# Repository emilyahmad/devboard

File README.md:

# Devboard

A simple devboard with some cute curious george motifs - my first hardware project/PCB, built using @KaiPereira's starter guide on stasis. Like any good devboard, the monkeyboard contains an SoC, memory, power management and I/O interfaces: it receives power via its USB-C connector port, maintains a quad SPI flash memory IC for data storage, 2 multipurpose switches, a crystal oscillator for precise electrical frequencies, and the star of the show, the RP2040 as its MCU.

### Assembled

| Front                              | Back                                 | Plugged in                               |
| ---------------------------------- | ------------------------------------ | ---------------------------------------- |
|  |  |  |

### Design

| Schematic                                                                                             | PCB                                                                                       | 3D Render                                                                                     |
| ----------------------------------------------------------------------------------------------------- | ----------------------------------------------------------------------------------------- | --------------------------------------------------------------------------------------------- |
|  |  |  |

### BOM

| Item                                 | Purpose                      | Quantity | Cost    | Source                               |
| ------------------------------------ | ---------------------------- | -------- | ------- | ------------------------------------ |
| C1, C2                               | 10uF decoupling capacitor    | 2        | $0.0800 | JLCPCB Basic (CL10A106KP8NNNC)       |
| C3, C18                              | 1uF decoupling capacitor     | 2        | $0.0660 | JLCPCB Extended (GRM155R60J105KE19D) |
| C4, C5, C19, C20, C22, C23, C24, C26 | 0.1uF decoupling capacitor   | 8        | $0.0845 | JLCPCB Basic (CL05B104KO5NNNC)       |
| C15, C16                             | 33pF crystal load capacitor  | 2        | $0.0130 | JLCPCB Basic (0402CG330J500NT)       |
| C17, C21, C25                        | 0.1uF decoupling capacitor   | 3        | $0.0845 | JLCPCB Basic (CL05B104KO5NNNC)       |
| J1                                   | USB-C receptacle             | 1        | $0.9155 | JLCPCB Extended (TYPE-C-31-M-12)     |
| J2, J3                               | 20-pin GPIO header           | 2        | —       | Solder yourself                      |
| J4                                   | 3-pin SWD debug header       | 1        | —       | Solder yourself                      |
| R1, R2                               | 5.1K CC pull-down resistor   | 2        | $0.0090 | JLCPCB Basic (0402WGF5101TCE)        |
| R3, R4                               | 27Ω USB termination resistor | 2        | $0.0176 | JLCPCB Extended (0402WGF270JTCE)     |
| R5, R7, R8                           | 1K resistor                  | 3        | $0.0150 | JLCPCB Extended (RCT021KFLF)         |
| R6                                   | 10K pull-up resistor         | 1        | $0.0065 | JLCPCB Basic (0402WGF1002TCE)        |
| SW1, SW2                             | Push button                  | 2        | $0.5550 | JLCPCB Basic (TS-1088-AR02016)       |
| U1                                   | MCP1700 3.3V LDO regulator   | 1        | $2.4285 | JLCPCB Extended (MCP1700T-3302E/TT)  |
| U2                                   | RP2040 microcontroller       | 1        | $4.8810 | JLCPCB Extended (RP2040)             |
| U3                                   | W25Q16 16Mbit flash memory   | 1        | $6.3910 | JLCPCB Extended (W25Q16JVZPIQ TR)    |
| Y1                                   | 12MHz crystal oscillator     | 1        | $0.8382 | JLCPCB Extended (XJHCELNANF-12MHZ)   |

Total: $16.38

<!--
reference
|RP2040|$0.94|https://www.lcsc.com/product-detail/C2040.html?s_z=s_p_RP2040&spm=wm.ssy.bg.0.xh&lcsc_vid=E1ENUAdXFlVdBAVSQFBZUQJQRFEMVgIFEgVcAgBRQgQxVlNRQFNbUVBfR1haUjsOAxUeFF5JWBYZEEoKFBINSQcJGk4%3D|
|Crystal oscillator|$0.07|https://www.lcsc.com/product-detail/C9002.html?s_z=s_q_CRYSTAL%252012MHZ&spm=wm.ssy.bg.0.xh&lcsc_vid=E1ENUAdXFlVdBAVSQFBZUQJQRFEMVgIFEgVcAgBRQgQxVlNRQFNbUVFTRlVXXzsOAxUeFF5JWBYZEEoKFBINSQcJGk4eFQsCAgIaSgADAwAHC0slRVFaV0oOAwwC|
|MCP1700 LDO, 3.3V|$0.98|https://www.lcsc.com/product-detail/C39051.html?s_z=n_q_mcp1700%2520tt&spm=wm.ssy.bg.16.xh&lcsc_vid=E1ENUAdXFlVdBAVSQFBZUQJQRFEMVgIFEgVcAgBRQgQxVlNRQFNbUVJRR1hcXjsOAxUeFF5JWBYZEEoKFBINSQcJGk4dAgUUFAk%3D|
|USB-C port, 16-pin|$0.08|https://www.lcsc.com/product-detail/C2988369.html?s_z=n_q_usb%2520c%252016&spm=wm.ssy.bg.0.xh&lcsc_vid=E1ENUAdXFlVdBAVSQFBZUQJQRFEMVgIFEgVcAgBRQgQxVlNRQFNbUVNSRVVYVzsOAxUeFF5JWBYZEEoKFBINSQcJGk4eFQsCAgIaSgADAwAHC0slRFheUlVIHxUDCw%3D%3D|
|W25Q128JVSIQ flash memory|$1.96|https://www.lcsc.com/product-detail/C97521.html?s_z=s_q_W25Q128JVSIQ&spm=wm.ssy.bg.0.xh&lcsc_vid=E1ENUAdXFlVdBAVSQFBZUQJQRFEMVgIFEgVcAgBRQgQxVlNRQFNbUVxWRFlWVTsOAxUeFF5JWBYZEEoKFBINSQcJGk4eFQsCAgIaSgADAwAHC0slRVhWX1dQTk8GEwkK|
|PCM5102A DAC|$1.02|https://www.lcsc.com/product-detail/C107671.html?s_z=n_q_pcm5102a&spm=wm.ssy.bg.1.xh&lcsc_vid=E1ENUAdXFlVdBAVSQFBZUQJQRFEMVgIFEgVcAgBRQgQxVlNRQFNbUV1XRVlaVjsOAxUeFF5JWBYZEEoKFBINSQcJGk4dAgUUFAk%3D|
|PAM8302AAD speaker amplifier|$0.21|https://www.lcsc.com/product-detail/C112137.html?s_z=n_q_pam8302aad&spm=wm.ssy.bg.0.xh&lcsc_vid=E1ENUAdXFlVdBAVSQFBZUQJQRFEMVgIFEgVcAgBRQgQxVlNRQFNbUV1SQFJbUzsOAxUeFF5JWBYZEEoKFBINSQcJGk4eFQsCAgIaSgADAwAHC0slRlFZUVNXWQkaCgg%3D|
|BQ25185 battery charging IC|$1.66|https://www.lcsc.com/product-detail/C19725033.html?s_z=s_p_BQ25185DLHR&spm=wm.ssy.bg.0.xh&lcsc_vid=E1ENUAdXFlVdBAVSQFBZUQJQRFEMVgIFEgVcAgBRQgQxVlNRQFNbUV1fQ1RWVzsOAxUeFF5JWBYZEEoKFBINSQcJGk4eFQsCAgIaSgADAwAHC0slRlBcVldRWQkaCgg%3D|
|SMD tactile switch, 6x6mm|$0.03|https://www.lcsc.com/product-detail/C49234152.html?s_z=n_q_5x5mm%2520button&spm=wm.ssy.bg.0.xh&lcsc_vid=RlQIVAdXEVQKUwJREwNdVlQAEQNaUAUCTlNbAgdURlMxVlNRQFJcUFFUTlhdUDsOAxUeFF5JWBYZEEoKFBINSQcJGk4%3D|
|Pin headers|$0.38|https://www.lcsc.com/product-detail/C2938459.html?s_z=h_q_pin%2520headers%252001x20&spm=wm.ssy.bg.1.xh&lcsc_vid=RlQIVAdXEVQKUwJREwNdVlQAEQNaUAUCTlNbAgdURlMxVlNRQFJcX1dVQFdZVTsOAxUeFF5JWBYZEEoKFBINSQcJGk4eFQsCAgIaSgADAwAHC0slRVhdX1BUQ08GEwkK|
|PCB|$0.42|https://cart.jlcpcb.com/quote?stencilLayer=2&stencilWidth=21&stencilLength=54&stencilCounts=5&plateType=1|
|Stencil|$3.05|https://cart.jlcpcb.com/quote?stencilLayer=2&stencilWidth=21&stencilLength=54&stencilCounts=5&plateType=1|

Total: $10.81 ($7.76 w/o stencil)

# Notes

meow
-

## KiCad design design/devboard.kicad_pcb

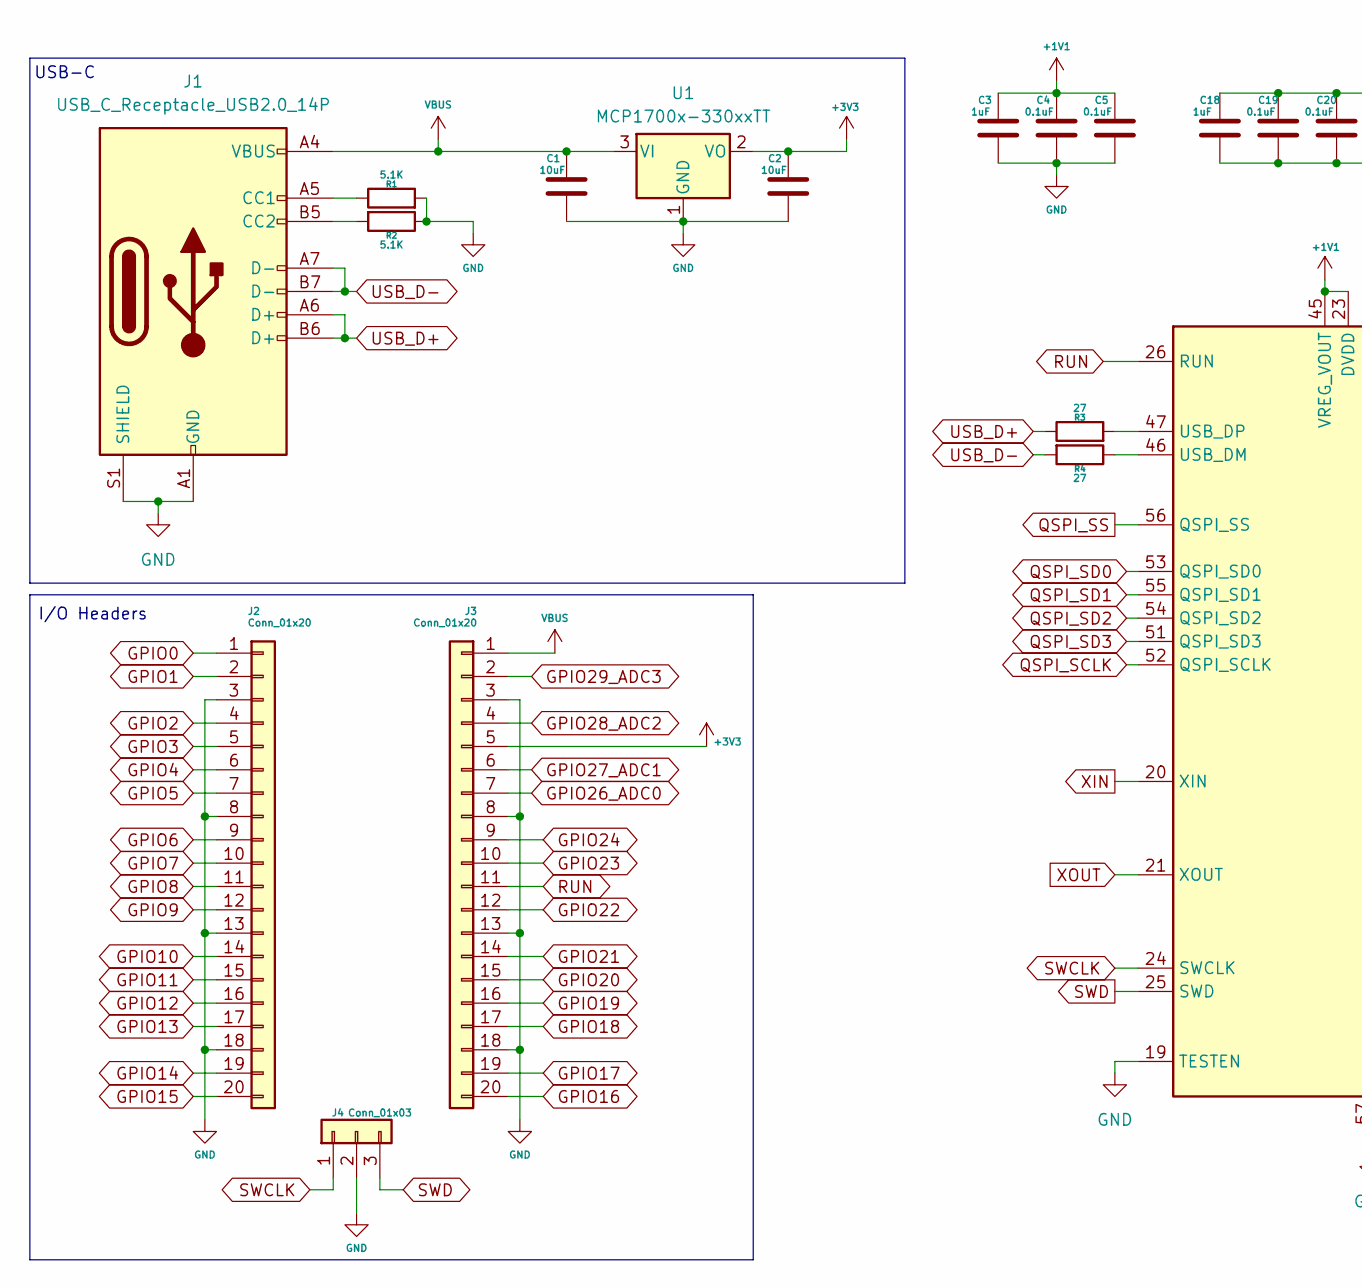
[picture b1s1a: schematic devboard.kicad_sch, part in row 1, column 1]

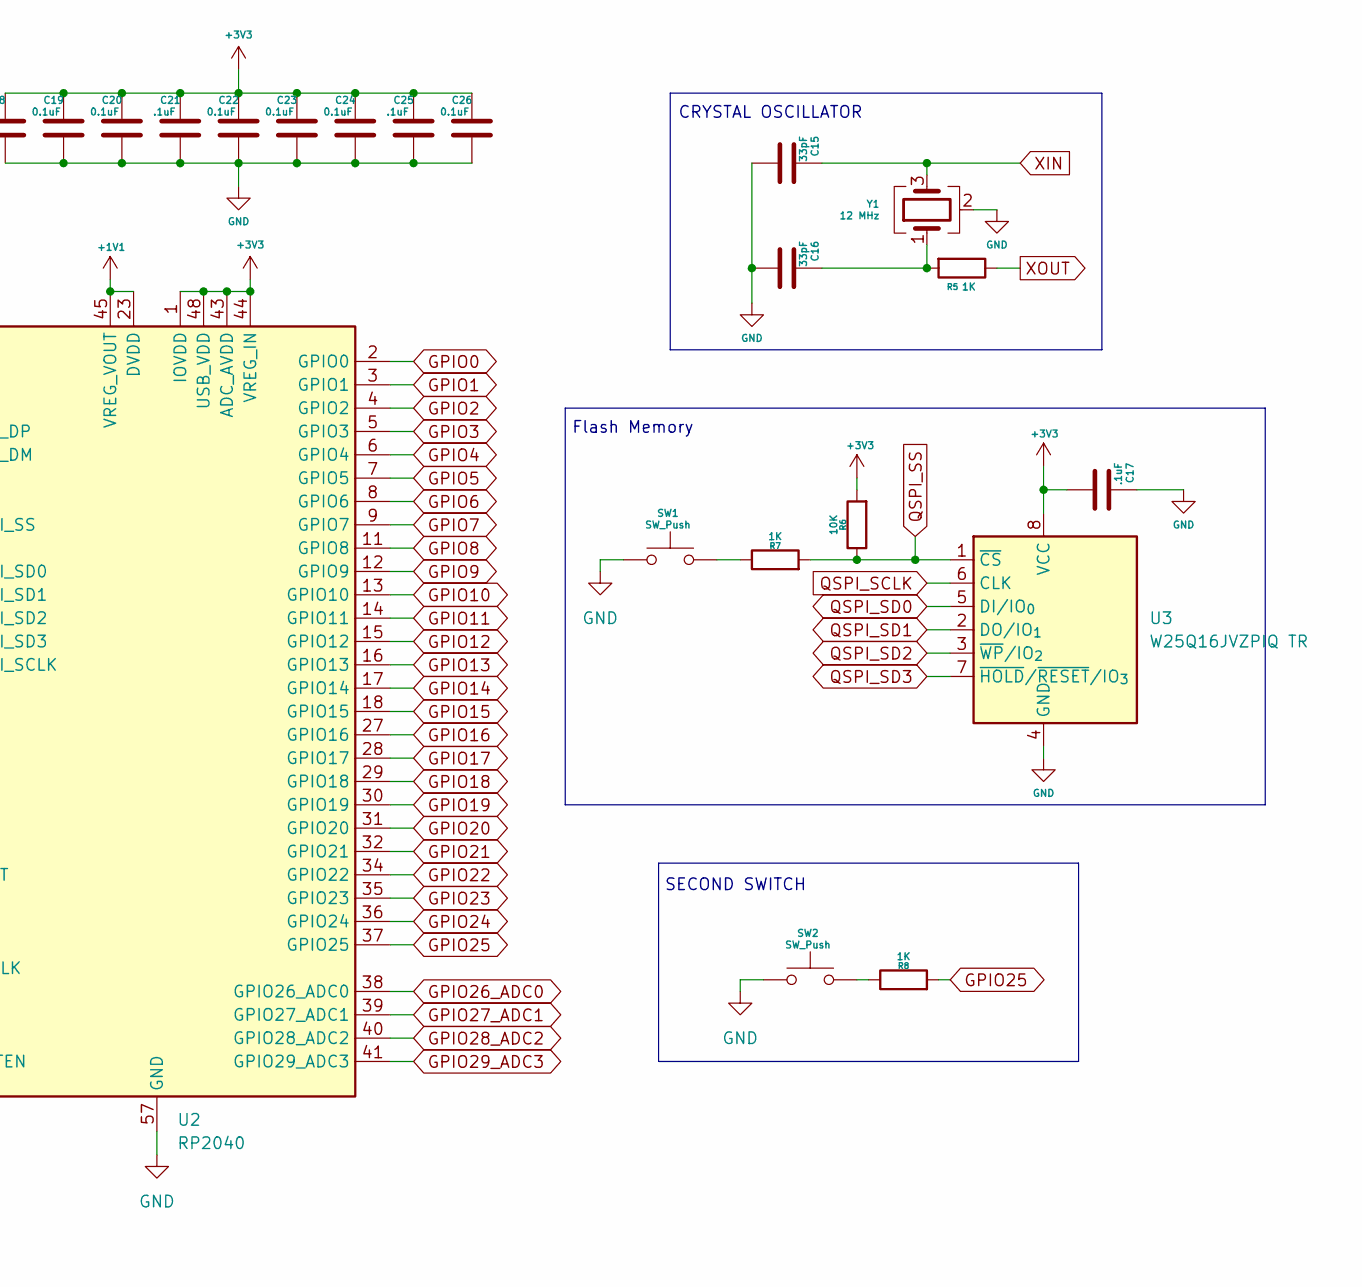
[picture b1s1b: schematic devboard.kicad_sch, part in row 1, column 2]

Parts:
C1, C2: 10uF; C_0201_0603Metric
C3, C18: 1uF; C_0402_1005Metric
C4, C5, C19, C20, C22, C23, C24, C26: 0.1uF; C_0402_1005Metric
C15, C16: 33pF; C_0402_1005Metric
C17, C21, C25: .1uF; C_0402_1005Metric
J1: USB_C_Receptacle_USB2.0_14P; USB_C_Receptacle_HRO_TYPE-C-31-M-12
J2, J3: Conn_01x20; PinHeader_1x20_P2.54mm_Vertical
J4: Conn_01x03; PinHeader_1x03_P2.54mm_Vertical
R1, R2: 5.1K; C_0402_1005Metric
R3, R4: 27; C_0402_1005Metric
R5, R7, R8: 1K; C_0402_1005Metric
R6: 10K; C_0402_1005Metric
SW1, SW2: SW_Push; SW_Push_SPST_NO_Alps_SKRK
U1: MCP1700x-330xxTT; SOT-23
U2: RP2040; QFN-56-1EP_7x7mm_P0.4mm_EP3.2x3.2mm
U3: W25Q16JVZPIQ TR; Winbond_USON-8-1EP_3x2mm_P0.5mm_EP0.2x1.6mm
Y1: 12 MHz; Crystal_SMD_3225-4Pin_3.2x2.5mm

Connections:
+1V1: C3.2, C4.2, C5.2, U2.23 (DVDD), U2.45 (VREG_VOUT), U2.50 (DVDD)
+3V3: C2.2, C17.1, C18.2, C19.2, C20.2, C21.2, C22.2, C23.2, C24.2, C25.2, C26.2, J3.5, R6.2, U1.2 (VO), U2.1 (IOVDD), U2.10 (IOVDD), U2.22 (IOVDD), U2.33 (IOVDD), U2.42 (IOVDD), U2.43 (ADC_AVDD), U2.44 (VREG_IN), U2.48 (USB_VDD), U2.49 (IOVDD), U3.8 (VCC)
GND: C1.1, C2.1, C3.1, C4.1, C5.1, C15.1, C16.1, C17.2, C18.1, C19.1, C20.1, C21.1, C22.1, C23.1, C24.1, C25.1, C26.1, J1.A1 (GND), J1.A12 (GND), J1.B1 (GND), J1.B12 (GND), J1.S1 (SHIELD), J2.3, J2.8, J2.13, J2.18, J3.3, J3.8, J3.13, J3.18, J4.2, R1.2, R2.1, SW1.1, SW2.1, U1.1 (GND), U2.19 (TESTEN), U2.57 (GND), U3.4 (GND), Y1.2 (G), Y1.4 (G)
GPIO0: J2.1, U2.2 (GPIO0)
GPIO1: J2.2, U2.3 (GPIO1)
GPIO2: J2.4, U2.4 (GPIO2)
GPIO3: J2.5, U2.5 (GPIO3)
GPIO4: J2.6, U2.6 (GPIO4)
GPIO5: J2.7, U2.7 (GPIO5)
GPIO6: J2.9, U2.8 (GPIO6)
GPIO7: J2.10, U2.9 (GPIO7)
GPIO8: J2.11, U2.11 (GPIO8)
GPIO9: J2.12, U2.12 (GPIO9)
GPIO10: J2.14, U2.13 (GPIO10)
GPIO11: J2.15, U2.14 (GPIO11)
GPIO12: J2.16, U2.15 (GPIO12)
GPIO13: J2.17, U2.16 (GPIO13)
GPIO14: J2.19, U2.17 (GPIO14)
GPIO15: J2.20, U2.18 (GPIO15)
GPIO16: J3.20, U2.27 (GPIO16)
GPIO17: J3.19, U2.28 (GPIO17)
GPIO18: J3.17, U2.29 (GPIO18)
GPIO19: J3.16, U2.30 (GPIO19)
GPIO20: J3.15, U2.31 (GPIO20)
GPIO21: J3.14, U2.32 (GPIO21)
GPIO22: J3.12, U2.34 (GPIO22)
GPIO23: J3.10, U2.35 (GPIO23)
GPIO24: J3.9, U2.36 (GPIO24)
GPIO25: R8.2, U2.37 (GPIO25)
GPIO26_ADC0: J3.7, U2.38 (GPIO26_ADC0)
GPIO27_ADC1: J3.6, U2.39 (GPIO27_ADC1)
GPIO28_ADC2: J3.4, U2.40 (GPIO28_ADC2)
GPIO29_ADC3: J3.2, U2.41 (GPIO29_ADC3)
unnamed: C16.2, R5.2, Y1.1
unnamed: J1.A5 (CC1), R1.1
unnamed: J1.B5 (CC2), R2.2
unnamed: R7.1, SW1.2
unnamed: R8.1, SW2.2
unnamed: R4.1, U2.46 (USB_DM)
unnamed: R3.2, U2.47 (USB_DP)
QSPI_SCLK: U2.52 (QSPI_SCLK), U3.6 (CLK)
QSPI_SD0: U2.53 (QSPI_SD0), U3.5 (DI/IO_{0})
QSPI_SD1: U2.55 (QSPI_SD1), U3.2 (DO/IO_{1})
QSPI_SD2: U2.54 (QSPI_SD2), U3.3 (~WP/IO_{2})
QSPI_SD3: U2.51 (QSPI_SD3), U3.7 (~HOLD/~RESET/IO_{3})
QSPI_SS: R6.1, R7.2, U2.56 (QSPI_SS), U3.1 (~CS)
RUN: J3.11, U2.26 (RUN)
SWCLK: J4.1, U2.24 (SWCLK)
SWD: J4.3, U2.25 (SWD)
USB_D+: J1.A6 (D+), J1.B6 (D+), R3.1
USB_D-: J1.A7 (D-), J1.B7 (D-), R4.2
VBUS: C1.2, J1.A4 (VBUS), J1.A9 (VBUS), J1.B4 (VBUS), J1.B9 (VBUS), J3.1, U1.3 (VI)
XIN: C15.2, U2.20 (XIN), Y1.3
XOUT: R5.1, U2.21 (XOUT)

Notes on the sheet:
USB-C
SECOND SWITCH
Flash Memory
CRYSTAL OSCILLATOR
I/O Headers

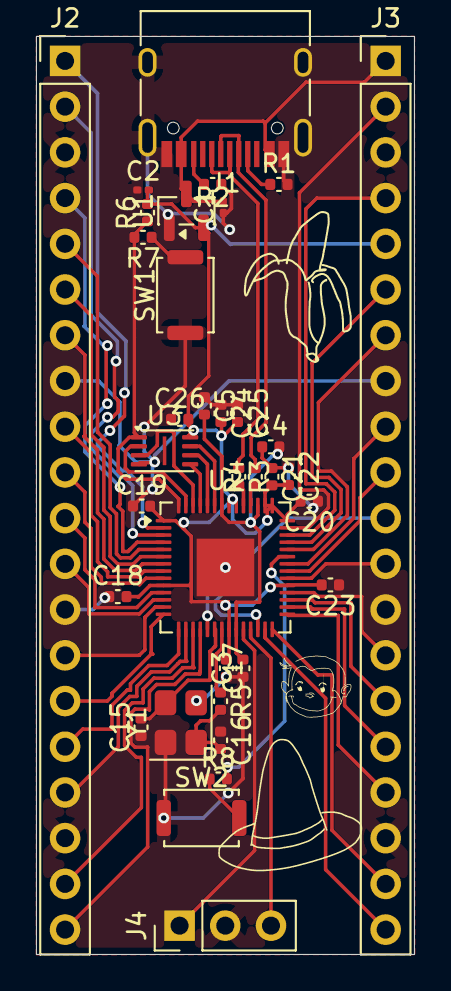
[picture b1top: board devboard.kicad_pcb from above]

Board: 2 copper layers, 21.0 x 51.0 mm, 35 parts (0 on the bottom side), 54 nets.

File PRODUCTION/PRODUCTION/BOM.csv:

Id,Designator,Footprint,Quantity,Comment,Supplier and ref
1,"C1, C2",C_0201_0603Metric,2,10uF,
2,"C3, C18",C_0402_1005Metric,2,1uF,
3,"C4, C5, C19, C20, C22, C23, C24, C26",C_0402_1005Metric,8,0.1uF,
4,"C15, C16",C_0402_1005Metric,2,33pF,
5,"C17, C21, C25",C_0402_1005Metric,3,.1uF,
6,J1,USB_C_Receptacle_HRO_TYPE-C-31-M-12,1,USB_C_Receptacle_USB2.0_14P,
7,"J2, J3",PinHeader_1x20_P2.54mm_Vertical,2,Conn_01x20,
8,J4,PinHeader_1x03_P2.54mm_Vertical,1,Conn_01x03,
9,"R1, R2",C_0402_1005Metric,2,5.1K,
10,"R3, R4",C_0402_1005Metric,2,27,
11,"R5, R7, R8",C_0402_1005Metric,3,1K,
12,R6,C_0402_1005Metric,1,10K,
13,"SW1, SW2",SW_Push_SPST_NO_Alps_SKRK,2,SW_Push,
14,U1,SOT-23,1,MCP1700x-330xxTT,
15,U2,QFN-56-1EP_7x7mm_P0.4mm_EP3.2x3.2mm,1,RP2040,
16,U3,Winbond_USON-8-1EP_3x2mm_P0.5mm_EP0.2x1.6mm,1,W25Q16JVZPIQ TR,
17,Y1,Crystal_SMD_3225-4Pin_3.2x2.5mm,1,12 MHz,

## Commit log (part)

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2026-05-03 i dont even know what she saying cuz she foreign 😛
2026-05-03 adding images
    Added schematic, PCB, and 3D viewer images to README.
2026-05-03 images for readme
2026-05-03 adding tables for images
    Updated project name and added detailed sections for schematic, PCB, and photos.
2026-05-03 fix images
    Updated image links in the README to use raw GitHub URLs.
2026-05-03 image fix
2026-05-03 fix format lol
2026-05-03 check if tble works
2026-05-03 added BOM
2026-05-03 Improve project description in README.md
2026-05-04 Enhance README with project details and ASCII art
    Updated the README to include an ASCII art representation of the project and enhanced the project description with more details about its components and features.
2026-05-04 readme update
2026-05-04 organized files
2026-05-04 fixed imgs
2026-05-04 readme
2026-05-31 not done
2026-06-17 finally ordered it guys
